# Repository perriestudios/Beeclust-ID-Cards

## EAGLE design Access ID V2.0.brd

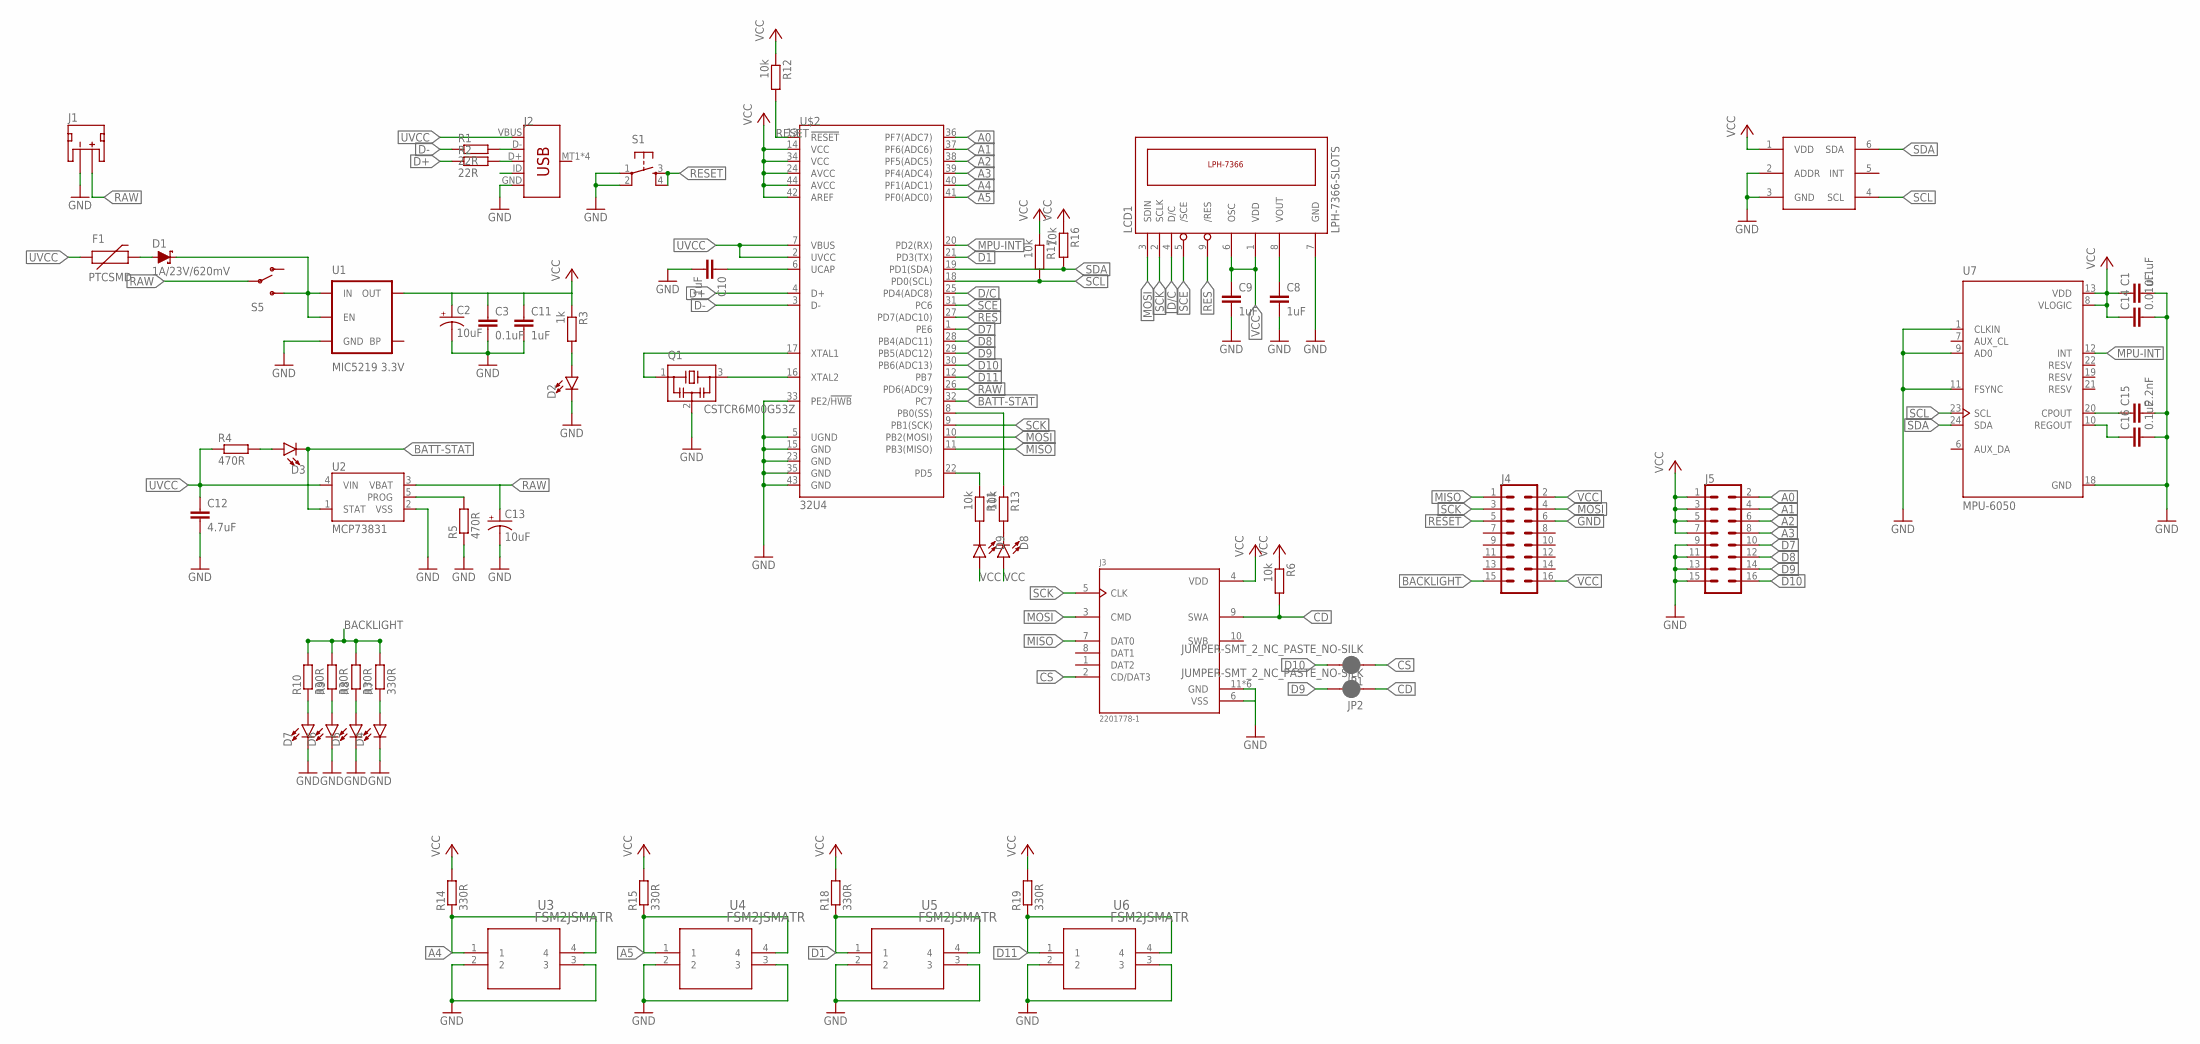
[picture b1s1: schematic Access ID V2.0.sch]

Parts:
C1, C3, C16: 0.1uF; C0603K
C2, C13: 10uF; EIA3216
C8, C9, C10, C11: 1uF; C0603K
C12: 4.7uF; C0603K
C14: 0.01uF; C0603K
C15: 2.2nF; C0603K
D1: 1A/23V/620mV; SOD-323
D2, D3, D4, D5, D6, D7, D8, D9: LED0603; LED-0603
F1: PTCSMD; PTC-1206
J1: JST_2MM_MALE; JST-2-SMD
J2: USB_MICRO-B_SMT; USB-MICROB
J3: 2201778-1; TE_2201778-1
J4, J5: CONN_08X2; 2X8
JP1, JP2: JUMPER-SMT_2_NC_PASTE_NO-SILK; SMT-JUMPER_2_NC_PASTE_NO-SILK
LCD1: LPH-7366-SLOTS
Q1: CSTCR6M00G53Z; CSTCR6M
R1, R2: 22R; R0603
R3: 1k; R0603
R4, R5: 470R; R0603
R6, R11, R12, R13, R16, R17: 10k; R0603
R7, R8, R9, R10, R14, R15, R18, R19: 330R; R0603
S1: TAC_SWITCHSMD; TACTILE_SWITCH_SMD
S5: SWITCH-SPDT-SMD-A; SWITCH-SPST-SMD-A
U1: MIC5219 3.3V; SOT23-5
U2: MCP73831; SOT23-5
U3, U4, U5, U6: FSM2JSMATR; SWITCH_FSM2JSMAA
U7: MPU-6050; QFN50P400X400X95-24N
U$2: 32U4; QFN-44-NOPAD
U$3: TI-OPT3001

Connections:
A0: J5.2, U$2.36 (PF7(ADC7))
A1: J5.4, U$2.37 (PF6(ADC6))
A2: J5.6, U$2.38 (PF5(ADC5))
A3: J5.8, U$2.39 (PF4(ADC4))
A4: R14.1, U3.1, U3.4, U$2.40 (PF1(ADC1))
A5: R15.1, U4.1, U4.4, U$2.41 (PF0(ADC0))
BACKLIGHT: J4.15, R7.2, R8.2, R9.2, R10.2
BATT-STAT: D3.C, U2.1 (STAT), U$2.32 (PC7)
CD: J3.9 (SWA), JP2.1, R6.2
CS: J3.2 (CD/DAT3), JP1.1
D1: R18.1, U5.1, U5.4, U$2.21 (PD3(TX))
D7: J5.10, U$2.1 (PE6)
D8: J5.12, U$2.28 (PB4(ADC11))
D9: J5.14, JP2.2, U$2.29 (PB5(ADC12))
D10: J5.16, JP1.2, U$2.30 (PB6(ADC13))
D11: R19.1, U6.1, U6.4, U$2.12 (PB7)
D+: R2.1, U$2.4 (D+)
D-: R1.1, U$2.3 (D-)
D/C: LCD1.4 (D/C), U$2.25 (PD4(ADC8))
GND: C1.2, C2.-, C3.2, C8.2, C9.2, C10.2, C11.2, C12.2, C13.-, C14.2, C15.2, C16.2, D2.C, D4.C, D5.C, D6.C, D7.C, J1.1 (-), J2.GND, J3.6 (VSS), J3.11 (GND), J3.12 (GND), J3.13 (GND), J3.14 (GND), J3.15 (GND), J3.16 (GND), J4.6, J5.9, J5.11, J5.13, J5.15, LCD1.7 (GND), Q1.2, R5.1, S1.1, S1.2, U1.2 (GND), U2.2 (VSS), U3.2, U3.3, U4.2, U4.3, U5.2, U5.3, U6.2, U6.3, U7.1 (CLKIN), U7.9 (AD0), U7.11 (FSYNC), U7.18 (GND), U$2.5 (UGND), U$2.15 (GND), U$2.23 (GND), U$2.33 (PE2/!HWB), U$2.35 (GND), U$2.43 (GND), U$3.2 (ADDR), U$3.3 (GND)
MISO: J3.7 (DAT0), J4.1, U$2.11 (PB3(MISO))
MOSI: J3.3 (CMD), J4.4, LCD1.3 (SDIN), U$2.10 (PB2(MOSI))
MPU-INT: U7.12 (INT), U$2.20 (PD2(RX))
unnamed: C15.1, U7.20 (CPOUT)
unnamed: D3.A, R4.2
unnamed: C10.1, U$2.6 (UCAP)
unnamed: J2.D+, R2.2
unnamed: R5.2, U2.5 (PROG)
unnamed: D7.A, R10.1
unnamed: J2.D-, R1.2
unnamed: D6.A, R9.1
unnamed: C16.1, U7.10 (REGOUT)
unnamed: D1.C, S5.3 (S), U1.1 (IN), U1.3 (EN)
unnamed: D2.A, R3.2
unnamed: D5.A, R8.1
unnamed: C8.1, LCD1.8 (VOUT)
unnamed: D4.A, R7.1
unnamed: Q1.1, U$2.17 (XTAL1)
unnamed: D1.A, F1.2
unnamed: Q1.3, U$2.16 (XTAL2)
unnamed: R13.1, U$2.8 (PB0(SS))
unnamed: D9.C, R11.2
unnamed: R11.1, U$2.22 (PD5)
unnamed: D8.C, R13.2
RAW: C13.+, J1.2 (+), S5.2, U2.3 (VBAT), U$2.26 (PD6(ADC9))
RES: LCD1.9 (/RES), U$2.27 (PD7(ADC10))
RESET: J4.5, R12.2, S1.3, S1.4, U$2.13 (!RESET)
SCE: LCD1.5 (/SCE), U$2.31 (PC6)
SCK: J3.5 (CLK), J4.3, LCD1.2 (SCLK), U$2.9 (PB1(SCK))
SCL: R17.2, U7.23 (SCL), U$2.18 (PD0(SCL)), U$3.4 (SCL)
SDA: R16.2, U7.24 (SDA), U$2.19 (PD1(SDA)), U$3.6 (SDA)
UVCC: C12.1, F1.1, J2.VBUS, R4.1, U2.4 (VIN), U$2.2 (UVCC), U$2.7 (VBUS)
VCC: C1.1, C2.+, C3.1, C9.1, C11.1, C14.1, D8.A, D9.A, J3.4 (VDD), J4.2, J4.16, J5.1, J5.3, J5.5, J5.7, LCD1.1 (VDD), LCD1.6 (OSC), R3.1, R6.1, R12.1, R14.2, R15.2, R16.1, R17.1, R18.2, R19.2, U1.5 (OUT), U7.8 (VLOGIC), U7.13 (VDD), U$2.14 (VCC), U$2.24 (AVCC), U$2.34 (VCC), U$2.42 (AREF), U$2.44 (AVCC), U$3.1 (VDD)

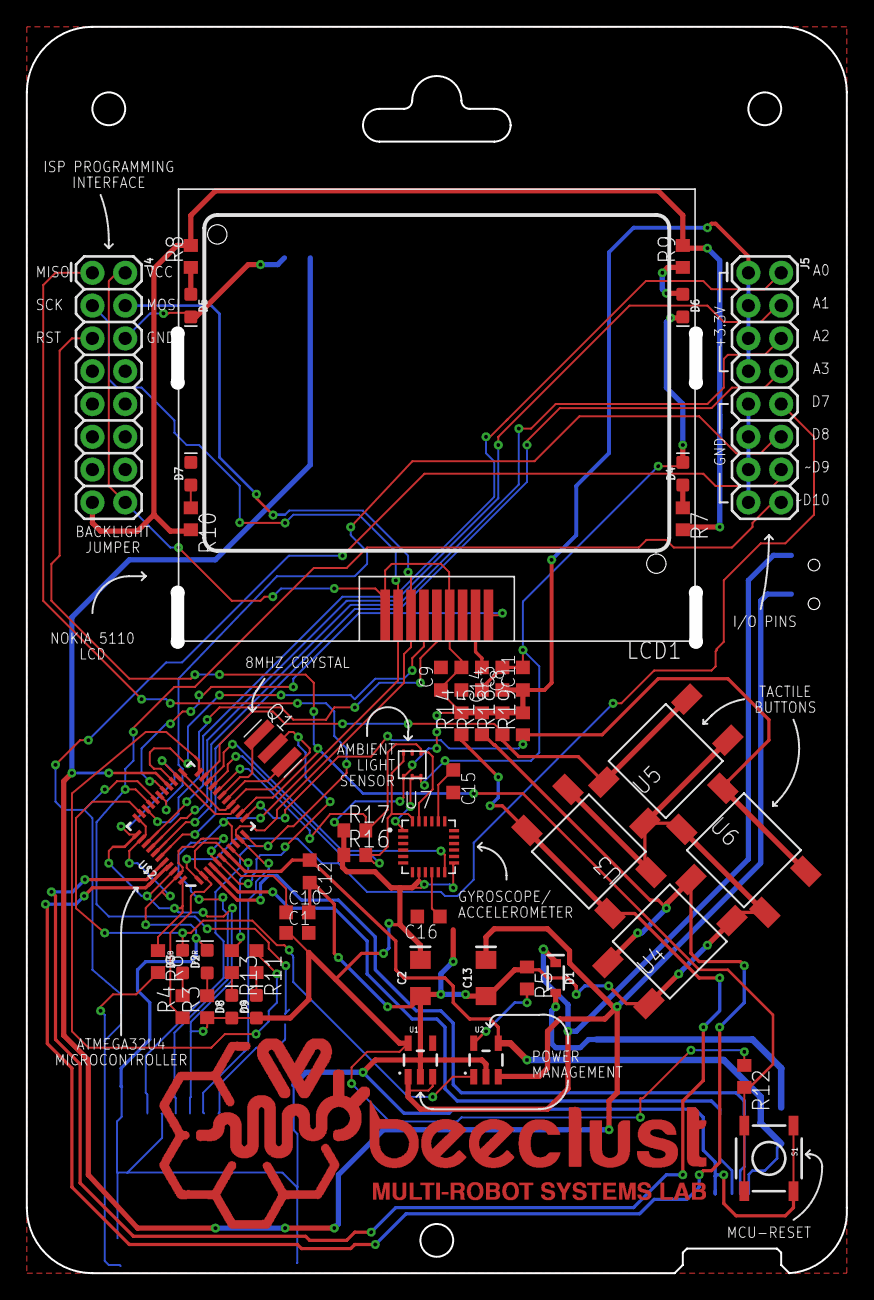
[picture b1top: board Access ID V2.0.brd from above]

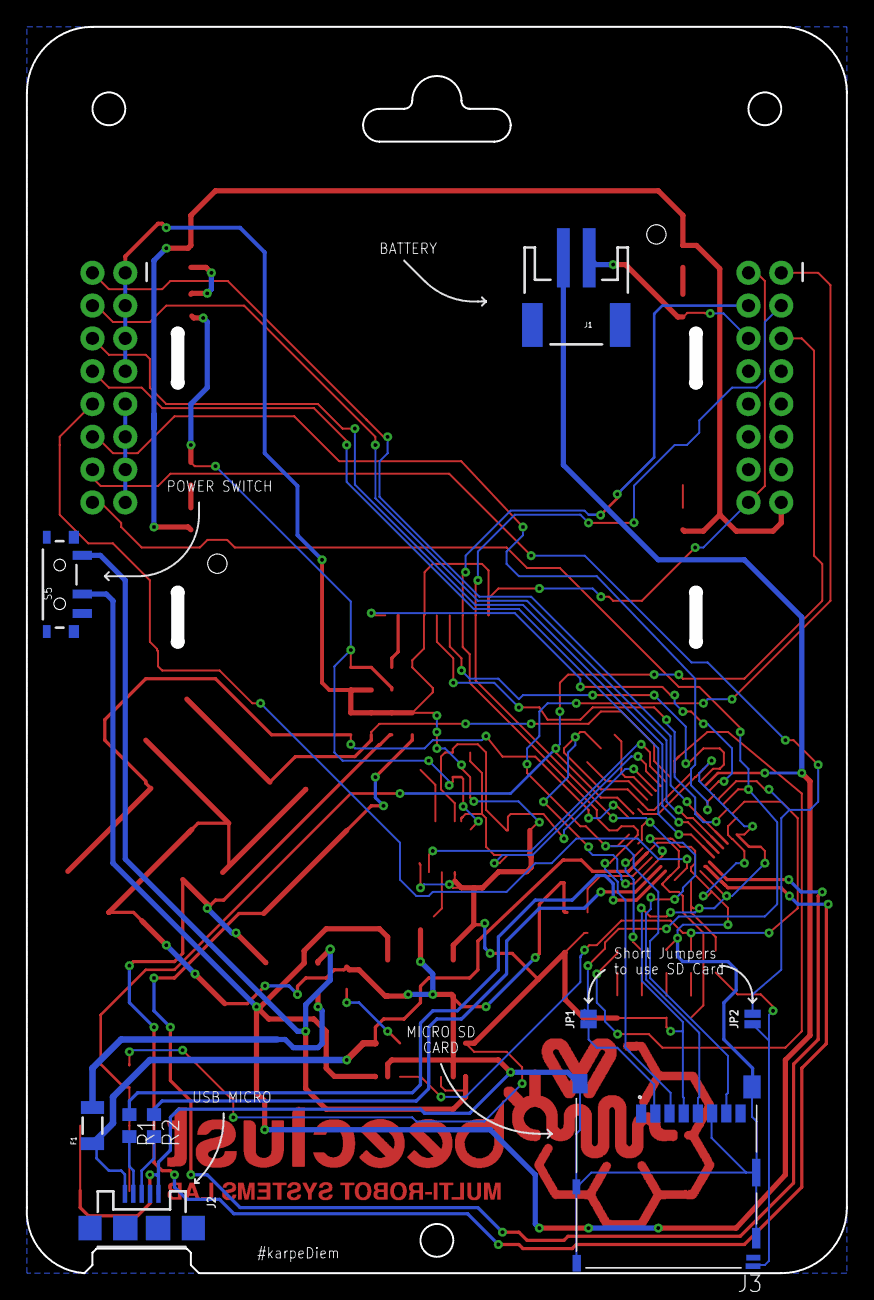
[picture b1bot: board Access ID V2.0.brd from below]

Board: 2 copper layers, 62.6 x 95.7 mm, 61 parts (9 on the bottom side), 53 nets.

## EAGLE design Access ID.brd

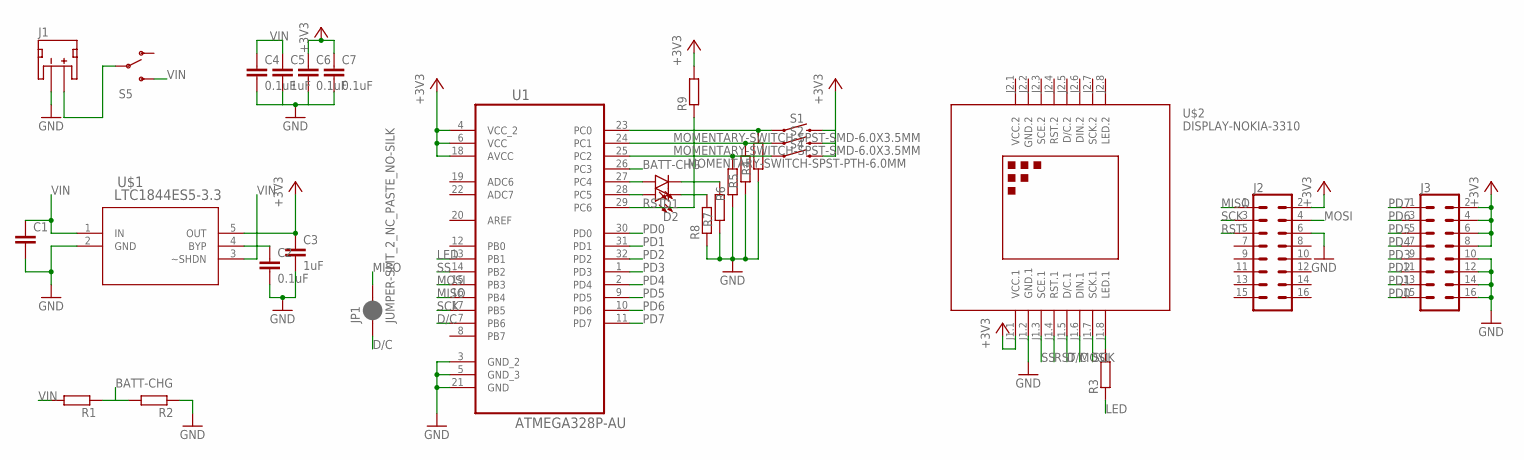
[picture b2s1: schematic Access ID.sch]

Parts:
C1: C-EUC0603K; C0603K
C2, C4, C6, C7: 0.1uF; C0603K
C3, C5: 1uF; C0603K
D1, D2: LED0603; LED-0603
J1: JST_2MM_MALE; JST-2-SMD
J2, J3: CONN_08X2; 2X8
JP1: JUMPER-SMT_2_NC_PASTE_NO-SILK; SMT-JUMPER_2_NC_PASTE_NO-SILK
R1, R2, R3, R4, R5, R6, R7, R8, R9: R-EU_R0603; R0603
S1, S2: MOMENTARY-SWITCH-SPST-SMD-6.0X3.5MM; TACTILE_SWITCH_SMD_6.0X3.5MM
S4: MOMENTARY-SWITCH-SPST-PTH-6.0MM; TACTILE_SWITCH_PTH_6.0MM
S5: SWITCH-SPDT-SMD-A; SWITCH-SPST-SMD-A
U1: ATMEGA328P-AU; QFP80P900X900X120-32N
U$1: LTC1844ES5-3.3; TSOT-23_S5
U$2: DISPLAY-NOKIA-3310

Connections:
+3V3: C3.1, C6.1, C7.1, J2.2, J3.2, J3.4, J3.6, J3.8, R9.2, S1.2, S2.2, S4.3 (2), U1.4 (VCC_2), U1.6 (VCC), U1.18 (AVCC), U$1.5 (OUT), U$2.J1.1 (VCC.1)
BATT-CHG: R1.1, R2.2, U1.26 (PC3)
D/C: JP1.1, U1.7 (PB6), U$2.J1.5 (D/C.1)
GND: C1.2, C2.2, C3.2, C4.2, C5.2, C6.2, C7.2, J1.1 (-), J2.6, J3.10, J3.12, J3.14, J3.16, R2.1, R4.1, R5.1, R6.1, R7.1, R8.1, U1.3 (GND_2), U1.5 (GND_3), U1.21 (GND), U$1.2 (GND), U$2.J1.2 (GND.1)
GND.2: U$2.J2.2 (GND.2)
LED: R3.1, U1.13 (PB1)
MISO: J2.1, JP1.2, U1.16 (PB4)
MOSI: J2.4, U1.15 (PB3), U$2.J1.6 (DIN.1)
unnamed: C2.1, U$1.4 (BYP)
unnamed: R3.2, U$2.J1.8 (LED.1)
unnamed: J1.2 (+), S5.2
unnamed: R5.2, S2.1, U1.24 (PC1)
unnamed: R6.2, S4.1, U1.25 (PC2)
unnamed: D2.C, R8.2
unnamed: R4.2, S1.1, U1.23 (PC0)
unnamed: D2.A, U1.28 (PC5)
unnamed: D1.A, U1.27 (PC4)
unnamed: D1.C, R7.2
PD0: J3.15, U1.30 (PD0)
PD1: J3.13, U1.31 (PD1)
PD2: J3.11, U1.32 (PD2)
PD3: J3.9, U1.1 (PD3)
PD4: J3.7, U1.2 (PD4)
PD5: J3.5, U1.9 (PD5)
PD6: J3.3, U1.10 (PD6)
PD7: J3.1, U1.11 (PD7)
RST: J2.5, R9.1, U1.29 (PC6), U$2.J1.4 (RST.1)
SCK: J2.3, U1.17 (PB5), U$2.J1.7 (SCK.1)
SS: U1.14 (PB2), U$2.J1.3 (SCE.1)
VCC.2: U$2.J2.1 (VCC.2)
VIN: C1.1, C4.1, C5.1, R1.2, S5.3 (S), U$1.1 (IN), U$1.3 (~SHDN)

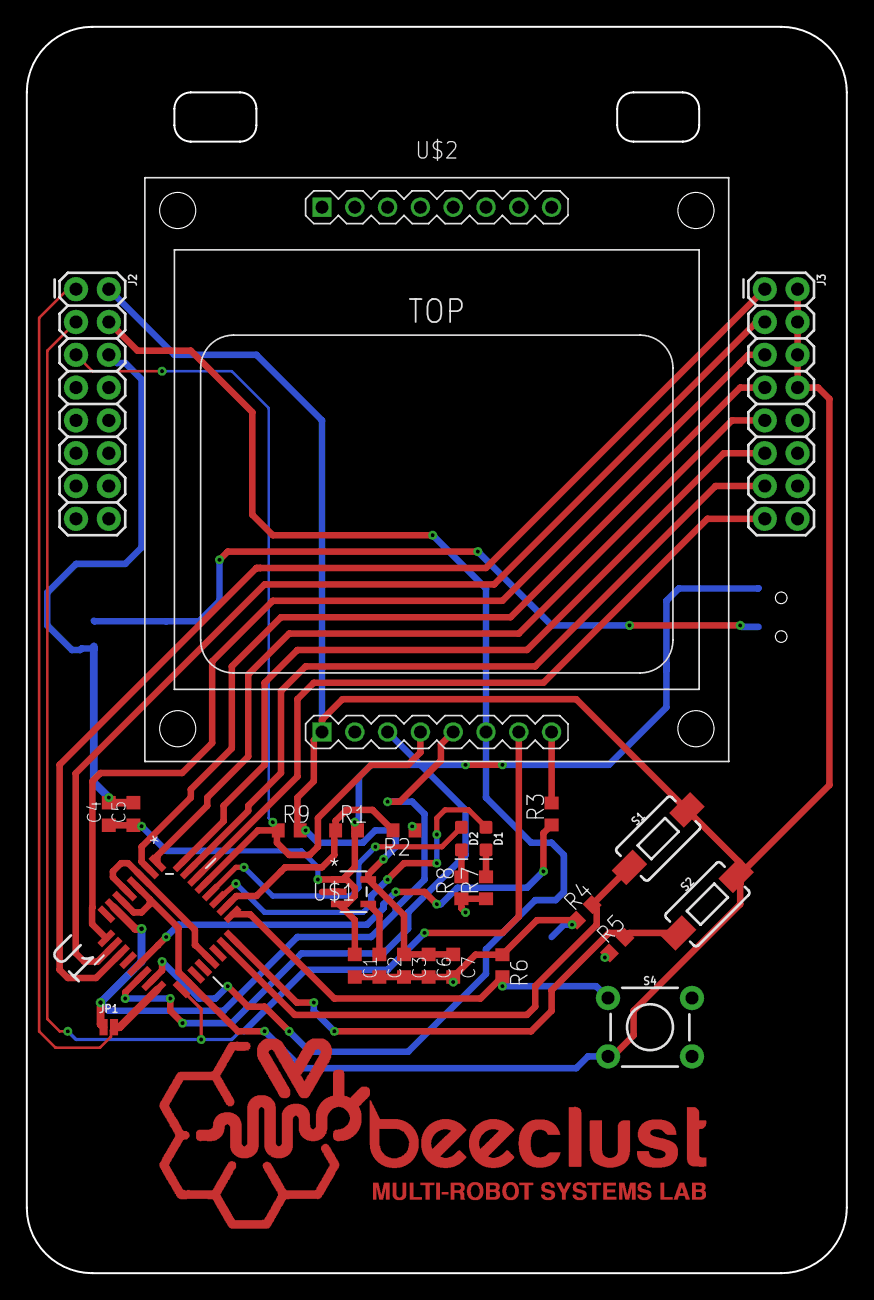
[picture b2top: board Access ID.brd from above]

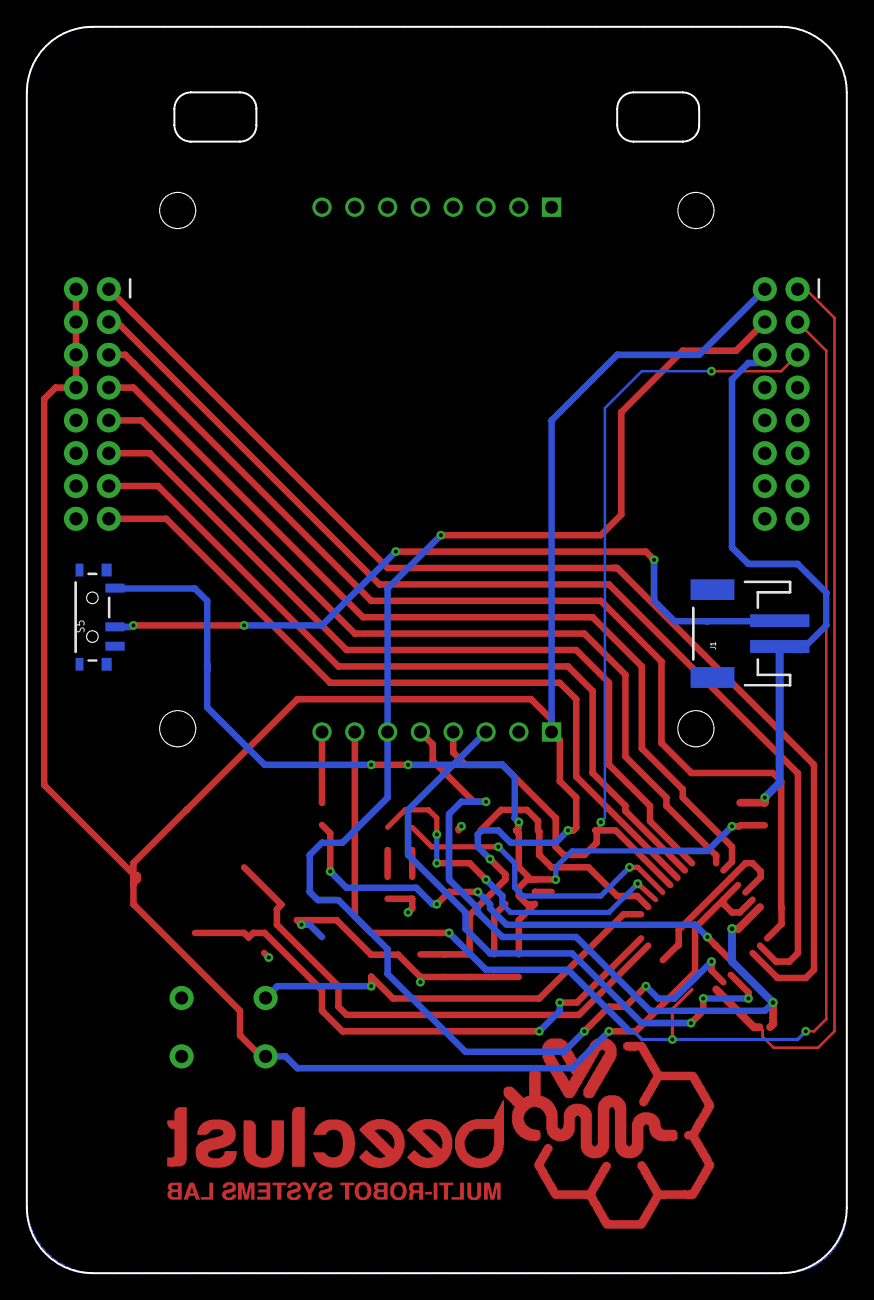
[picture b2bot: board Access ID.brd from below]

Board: 2 copper layers, 63.5 x 96.5 mm, 29 parts (2 on the bottom side), 29 nets.

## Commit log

2020-11-17 Added the files

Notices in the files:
parts and their libraries:
SparkFun-Connectors: Licensing: Creative Commons ShareAlike 4.0 International - https://creativecommons.org/licenses/by-sa/4.0
FaBo-Mems: Released under the Creative Commons Attribution-ShareAlike 4.0 License
https://creativecommons.org/licenses/by-sa/4.0
